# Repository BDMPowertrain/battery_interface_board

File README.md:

<h1 align="center">BATTERY_INTERFACE_BOARD</h1>
<p align="center">Battery Interface Board</p>
<p align="center"><em>This board interfaces with the cell tap connctons fusing them, and collecting them to one connector.</em></p>

<p align="center" width="100%">
  
</p>

***

<p align="center">
  
&nbsp; &nbsp; &nbsp; &nbsp;
  
</p>

***

## SPECIFICATIONS

| Parameter | Value |
| --- | --- |
| Dimensions | 300.0 × 47.0 mm |
| Company | Blue Devil Motor Sports |
| Designer | Aidan Brzezinski |
| Revision | 1.2.0+ (Unreleased) |

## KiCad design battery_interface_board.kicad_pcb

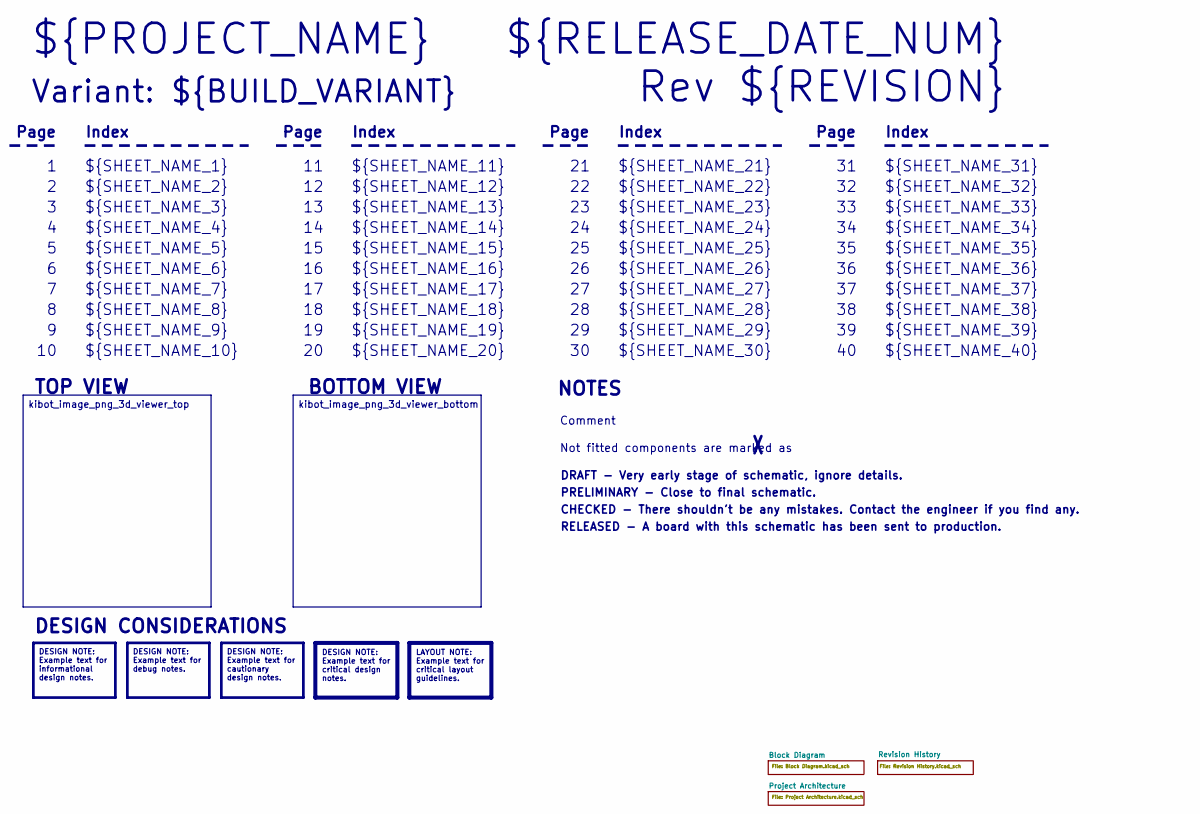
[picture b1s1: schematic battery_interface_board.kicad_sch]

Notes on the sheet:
Variant: ${BUILD_VARIANT}
RELEASED - A board with this schematic has been sent to production.
${SHEET_NAME_24}
Index
Page
PRELIMINARY - Close to final schematic.
${SHEET_NAME_22}
DRAFT - Very early stage of schematic, ignore details.
${SHEET_NAME_12}
${SHEET_NAME_8}
${SHEET_NAME_2}
${SHEET_NAME_5}
${SHEET_NAME_20}
${SHEET_NAME_23}
${RELEASE_DATE_NUM}
${SHEET_NAME_35}
Not fitted components are marked as
${SHEET_NAME_11}
${SHEET_NAME_6}
${SHEET_NAME_37}
${SHEET_NAME_26}
${SHEET_NAME_36}
Rev ${REVISION}
${SHEET_NAME_15}
CHECKED - There shouldn't be any mistakes. Contact the engineer if you find any.
BOTTOM VIEW
${SHEET_NAME_14}
${SHEET_NAME_21}
${SHEET_NAME_17}
${SHEET_NAME_18}
${SHEET_NAME_7}
${SHEET_NAME_31}
${PROJECT_NAME}
NOTES
${SHEET_NAME_40}
${SHEET_NAME_39}
${SHEET_NAME_32}
${SHEET_NAME_1}
${SHEET_NAME_9}
${SHEET_NAME_38}

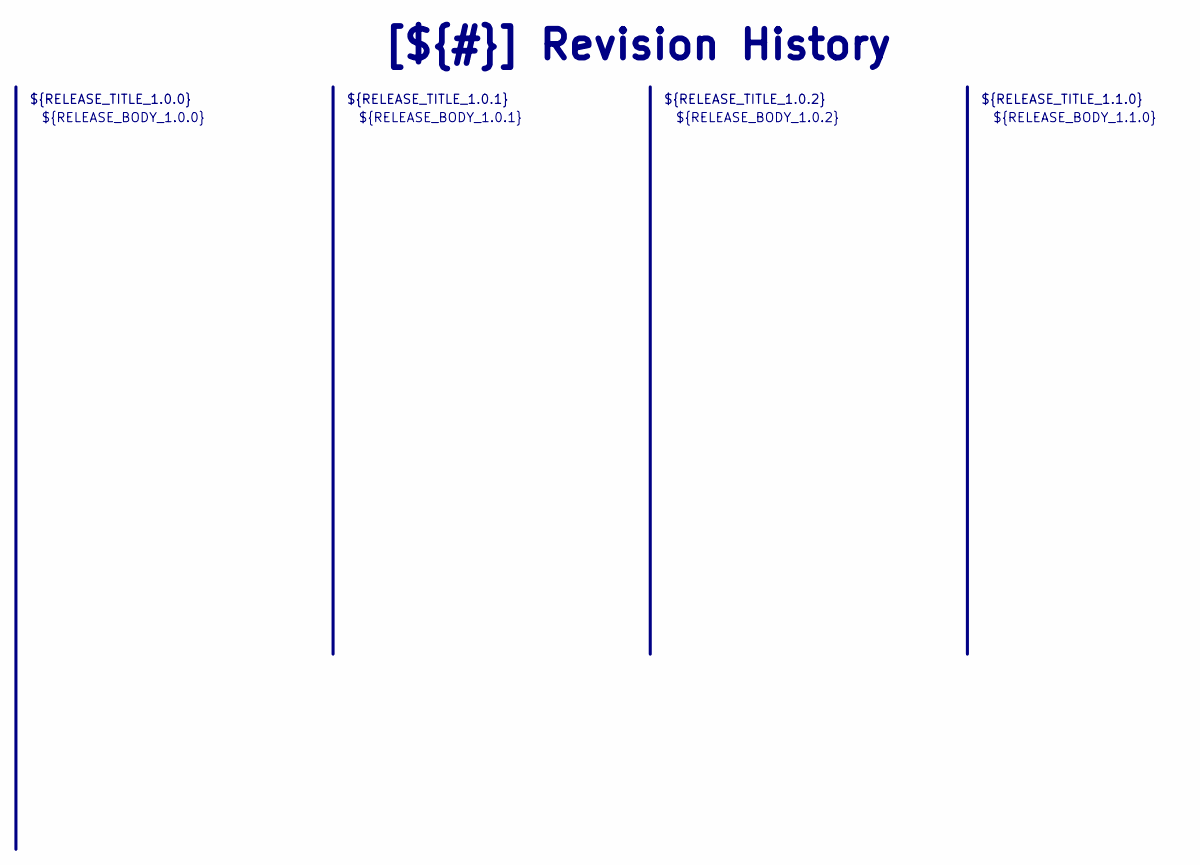
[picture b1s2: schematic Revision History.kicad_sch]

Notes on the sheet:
${RELEASE_BODY_1.1.0}
[${#}] ${TITLE}
${RELEASE_BODY_1.0.0}
${RELEASE_TITLE_1.0.2}
${RELEASE_BODY_1.0.2}
${RELEASE_BODY_1.0.1}
${RELEASE_TITLE_1.0.0}
${RELEASE_TITLE_1.0.1}
${RELEASE_TITLE_1.1.0}

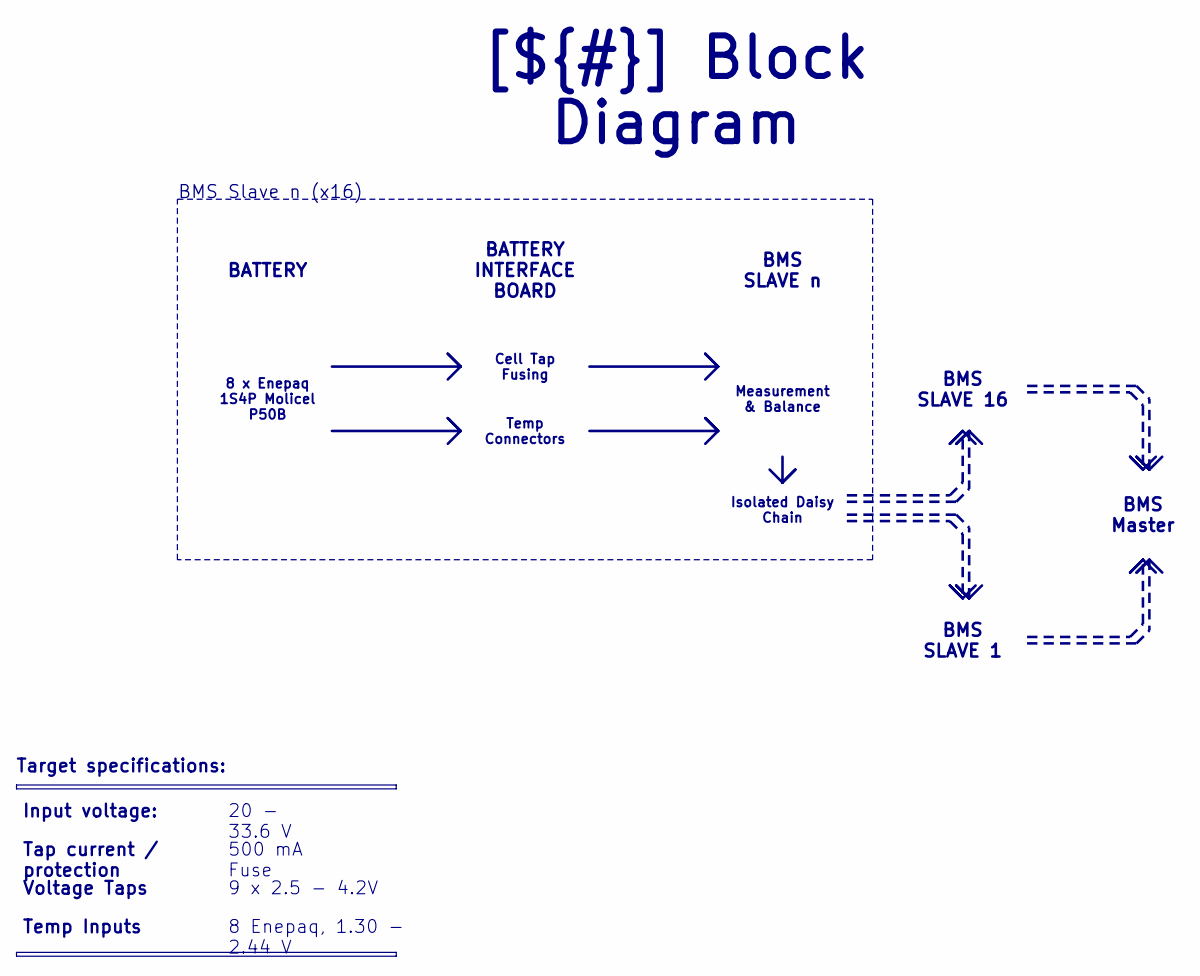
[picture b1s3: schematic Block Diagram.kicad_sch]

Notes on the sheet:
BMS Slave n (x16)
Temp Connectors
Voltage Taps
20 - 33.6 V
9 x 2.5 - 4.2V
BMS Master
BATTERY INTERFACE BOARD
Temp Inputs
Cell Tap Fusing
BMS SLAVE n
[${#}] ${TITLE}
Input voltage:
BMS SLAVE 1
Target specifications:
Isolated Daisy Chain
Tap current / protection
500 mA Fuse
BATTERY
8 x Enepaq 1S4P Molicel P50B
BMS SLAVE 16
8 Enepaq, 1.30 - 2.44 V
Measurement & Balance

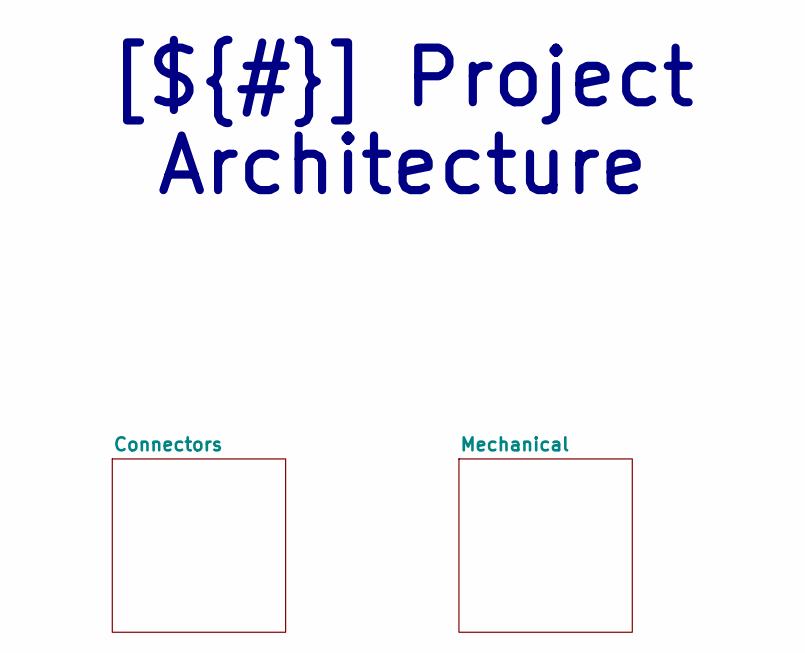
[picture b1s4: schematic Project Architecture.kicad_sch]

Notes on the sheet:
[${#}] ${TITLE}

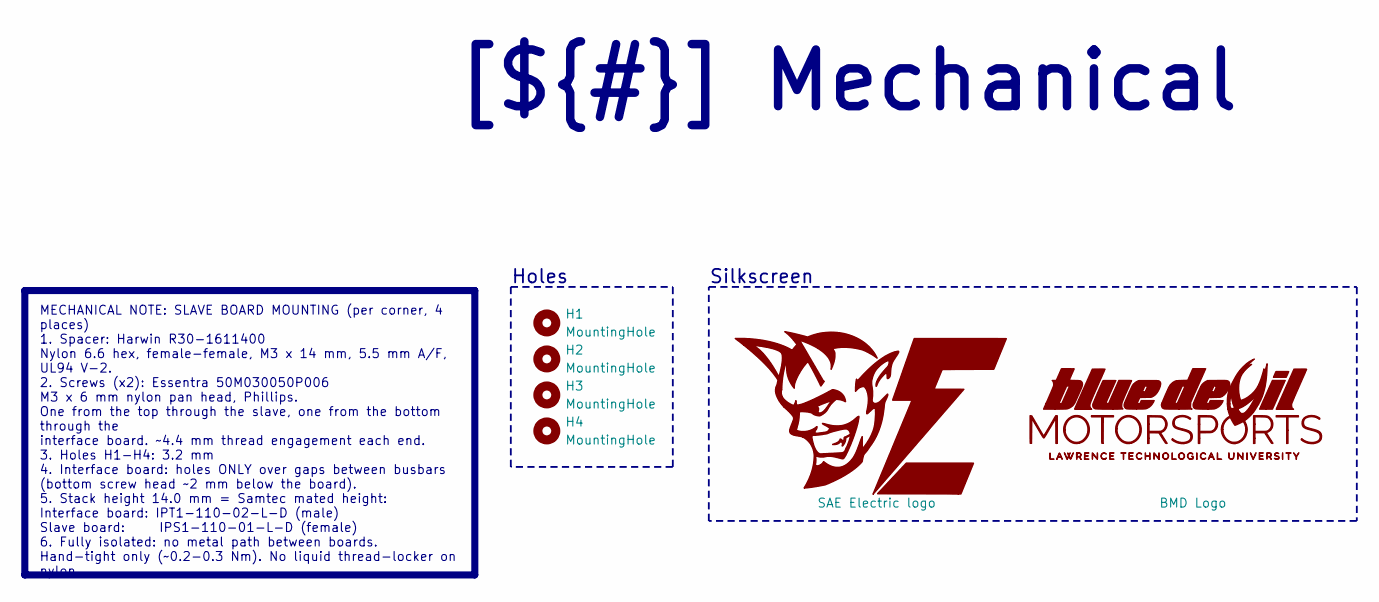
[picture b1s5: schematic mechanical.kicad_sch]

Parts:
G1: BMD Logo; BDM_Logo_40mm; Manufacturer Part Number BMD Logo
G2: SAE Electric logo; SAE_Electric_Logo_20mm; Manufacturer Part Number SAE Electric logo
H1, H2, H3, H4: MountingHole; MountingHole_3.2mm_M3_ISO7380

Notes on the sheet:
Silkscreen
Holes
MECHANICAL NOTE: SLAVE BOARD MOUNTING (per corner, 4 places) 1. Spacer: Harwin R30-1611400 Nylon 6.6 hex, female-female, M3 x 14 mm, 5.5 mm A/F, UL94 V-2. 2. Screws (x2): Essentra 50M030050P006 M3 x 6 mm nylon pan head, Phillips. One from the top through the slave, one from the bottom through the i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
[${#}] ${TITLE}

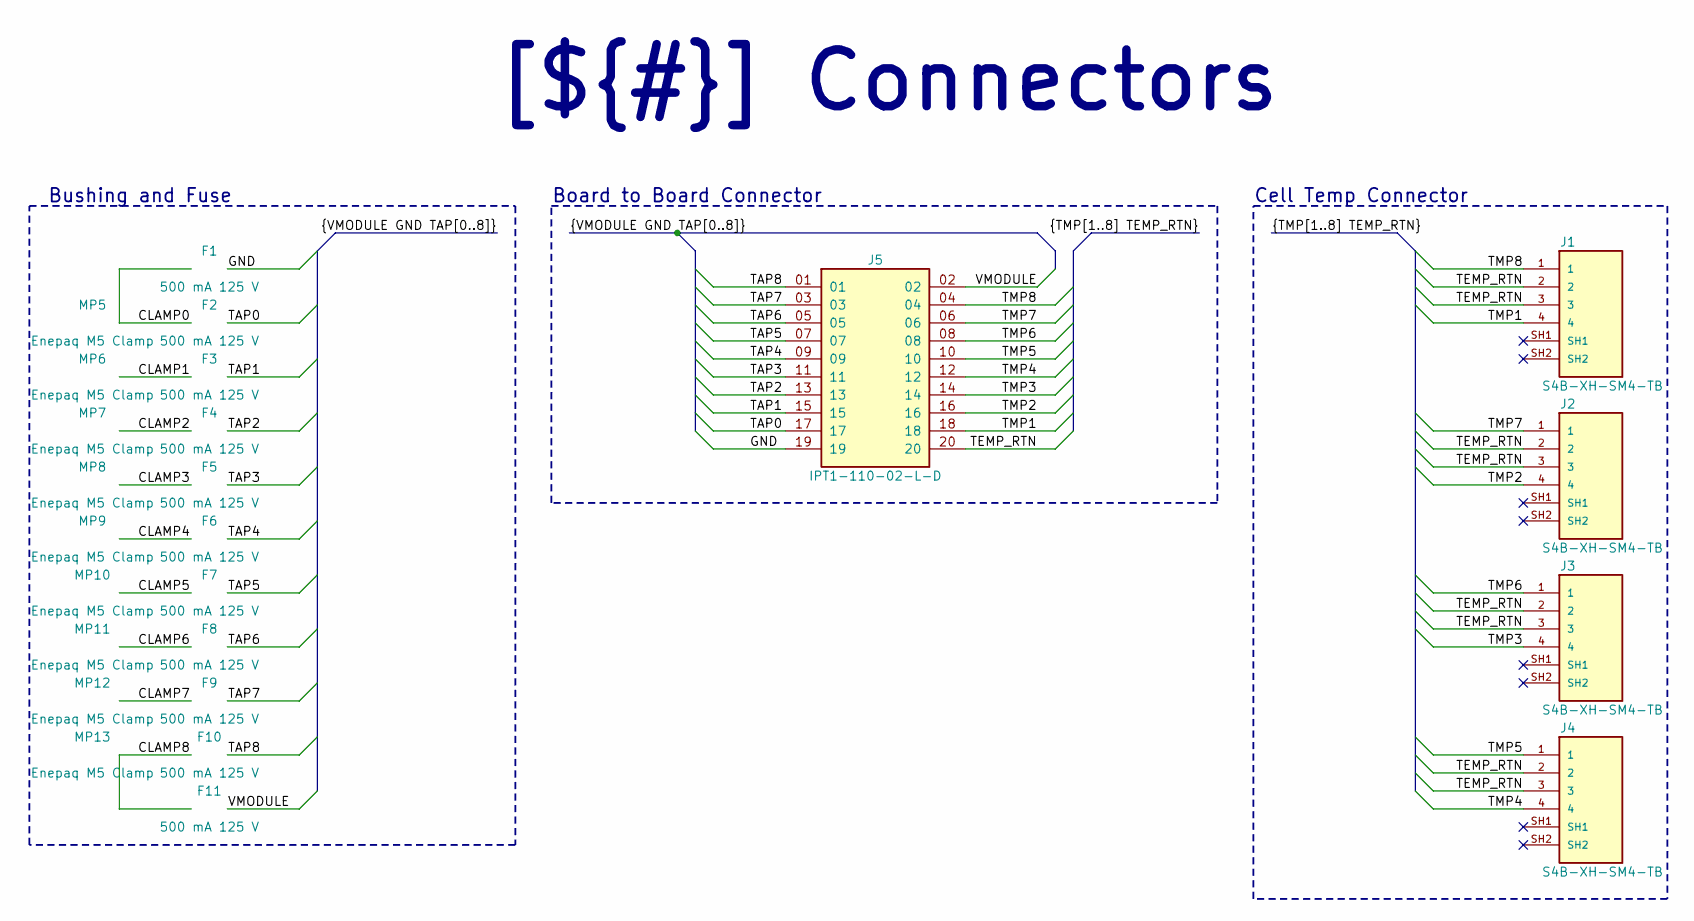
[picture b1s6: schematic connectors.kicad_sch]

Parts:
F1, F2, F3, F4, F5, F6, F7, F8, F9, F10, F11: 500 mA 125 V; 0451Series_LTF; Manufacturer Part Number 0451.500MRL
J1, J2, J3, J4: S4B-XH-SM4-TB; JST_S4B-XH-SM4-TB; PARTREV NA
J5: IPT1-110-02-L-D; SAMTEC_IPT1-110-02-L-D; PARTREV R
MP5, MP6, MP7, MP8, MP9, MP10, MP11, MP12, MP13: Enepaq M5 Clamp; Enepaq_M5_Clamp; Manufacturer Part Number Enepaq M5 Clamp

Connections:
/Project Architecture/Connectors/CLAMP0: F1.1, F2.1, MP5.1
/Project Architecture/Connectors/CLAMP1: F3.1, MP6.1
/Project Architecture/Connectors/CLAMP2: F4.1, MP7.1
/Project Architecture/Connectors/CLAMP3: F5.1, MP8.1
/Project Architecture/Connectors/CLAMP4: F6.1, MP9.1
/Project Architecture/Connectors/CLAMP5: F7.1, MP10.1
/Project Architecture/Connectors/CLAMP6: F8.1, MP11.1
/Project Architecture/Connectors/CLAMP7: F9.1, MP12.1
/Project Architecture/Connectors/CLAMP8: F10.1, F11.1, MP13.1
/Project Architecture/Connectors/GND: F1.2, J5.19
/Project Architecture/Connectors/TAP0: F2.2, J5.17
/Project Architecture/Connectors/TAP1: F3.2, J5.15
/Project Architecture/Connectors/TAP2: F4.2, J5.13
/Project Architecture/Connectors/TAP3: F5.2, J5.11
/Project Architecture/Connectors/TAP4: F6.2, J5.09
/Project Architecture/Connectors/TAP5: F7.2, J5.07
/Project Architecture/Connectors/TAP6: F8.2, J5.05
/Project Architecture/Connectors/TAP7: F9.2, J5.03
/Project Architecture/Connectors/TAP8: F10.2, J5.01
/Project Architecture/Connectors/TEMP_RTN: J1.2, J1.3, J2.2, J2.3, J3.2, J3.3, J4.2, J4.3, J5.20
/Project Architecture/Connectors/TMP1: J1.4, J5.18
/Project Architecture/Connectors/TMP2: J2.4, J5.16
/Project Architecture/Connectors/TMP3: J3.4, J5.14
/Project Architecture/Connectors/TMP4: J4.4, J5.12
/Project Architecture/Connectors/TMP5: J4.1, J5.10
/Project Architecture/Connectors/TMP6: J3.1, J5.08
/Project Architecture/Connectors/TMP7: J2.1, J5.06
/Project Architecture/Connectors/TMP8: J1.1, J5.04
/Project Architecture/Connectors/VMODULE: F11.2, J5.02

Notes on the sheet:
Cell Temp Connector
Bushing and Fuse
Board to Board Connector
[${#}] ${TITLE}

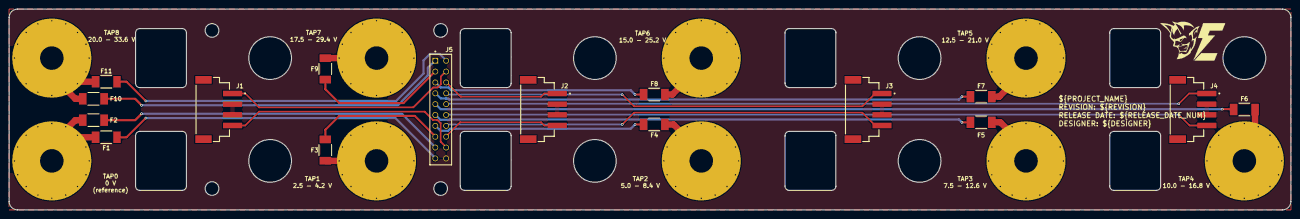
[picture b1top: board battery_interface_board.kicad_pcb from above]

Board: 2 copper layers, 300.0 x 47.0 mm, 31 parts (1 on the bottom side), 29 nets.

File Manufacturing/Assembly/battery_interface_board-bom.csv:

Row,Quantity Per PCB,References,Value,Datasheet,Footprint,Description,Manufacturer,Manufacturer Part Number,Supplier Part Number
1,11,F1 F2 F3 F4 F5 F6 F7 F8 F9 F10 F11,500 mA 125 V,https://www.littelfuse.com/assetdocs/littelfuse-fuse-451-453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,0451Series_LTF,"500 mA 125 V 125 V Fuse Board Mount (Cartridge Style Excluded) Surface Mount 2-SMD, Square End Block",Littelfuse Inc.,0451.500MRL,
2,1,G1,BMD Logo,N/A,BDM_Logo_40mm,Blue Devil Motorsports silkscreen logo.,BMD,BMD Logo,
3,1,G2,SAE Electric logo,N/A,SAE_Electric_Logo_20mm,SAE Electric logo.,BDM,SAE Electric logo,
4,1,J5,IPT1-110-02-L-D,https://mm.digikey.com/Volume0/opasdata/d220001/medias/docus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,SAMTEC_IPT1-110-02-L-D,"Connector Header Through Hole 20 position 0.100"" (2.54mm)",Samtec Samtec Inc.,IPT1-110-02-L-D,
5,4,J1 J2 J3 J4,S4B-XH-SM4-TB,https://mm.digikey.com/Volume0/opasdata/d220001/medias/docus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,JST_S4B-XH-SM4-TB,"Connector Header Surface Mount, Right Angle 4 position 0.098"" (2.50mm)",JST JST Sales America Inc.,S4B-XH-SM4-TB,
6,9,MP5 MP6 MP7 MP8 MP9 MP10 MP11 MP12 MP13,Enepaq M5 Clamp,N/A,Enepaq_M5_Clamp,"Enepaq M5 Clamp Through hole pad with via ring, sized for 15mm flat washer, 11mm bevel washer.",BDM,Enepaq M5 Clamp,
